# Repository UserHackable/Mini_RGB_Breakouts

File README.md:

## Mini_Arduino_3mm 

### Board dimensions

* (80000, 50000) original units
* (0.8000, 0.5000) inches
* (20.3200, 12.7000) mm

[gerbers](Mini_Arduino_3mm_gerber.zip?raw=true)

| Front | Back |
| --- | --- |
|  |  |

## Mini_Arduino_4mm_Oval 

### Board dimensions

* (80000, 50000) original units
* (0.8000, 0.5000) inches
* (20.3200, 12.7000) mm

[gerbers](Mini_Arduino_4mm_Oval_gerber.zip?raw=true)

| Front | Back |
| --- | --- |
|  |  |

## Mini_Arduino_5mm 

### Board dimensions

* (90000, 66246) original units
* (0.9000, 0.6625) inches
* (22.8600, 16.8265) mm

[gerbers](Mini_Arduino_5mm_gerber.zip?raw=true)

| Front | Back |
| --- | --- |
|  |  |

## Mini_Arduino_5mm_RGB 

### Board dimensions

* (80000, 50000) original units
* (0.8000, 0.5000) inches
* (20.3200, 12.7000) mm

[gerbers](Mini_Arduino_5mm_RGB_gerber.zip?raw=true)

| Front | Back |
| --- | --- |
|  |  |

## Mini_Oval 

### Board dimensions

* (65000, 60000) original units
* (0.6500, 0.6000) inches
* (16.5100, 15.2400) mm

[gerbers](Mini_Oval_gerber.zip?raw=true)

| Front | Back |
| --- | --- |
|  |  |

## Mini_RGB 

### Board dimensions

* (60000, 60000) original units
* (0.6000, 0.6000) inches
* (15.2400, 15.2400) mm

[gerbers](Mini_RGB_gerber.zip?raw=true)

| Front | Back |
| --- | --- |
|  |  |

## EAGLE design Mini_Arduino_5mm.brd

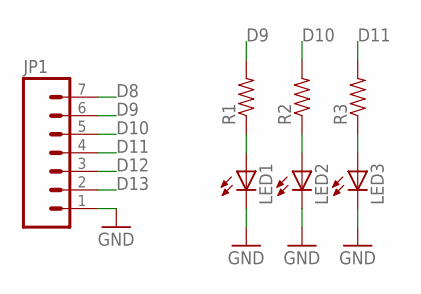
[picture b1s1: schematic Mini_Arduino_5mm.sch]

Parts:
JP1: M07; 1X07
LED1, LED2, LED3: LED5MM
R1, R2, R3: RESISTORAXIAL-0.3; AXIAL-0.3

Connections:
D8: JP1.7
D9: JP1.6, R1.P$2 (2)
D10: JP1.5, R2.P$2 (2)
D11: JP1.4, R3.P$2 (2)
D12: JP1.3
D13: JP1.2
GND: JP1.1, LED1.K (C), LED2.K (C), LED3.K (C)
unnamed: LED1.A, R1.P$1 (1)
unnamed: LED2.A, R2.P$1 (1)
unnamed: LED3.A, R3.P$1 (1)

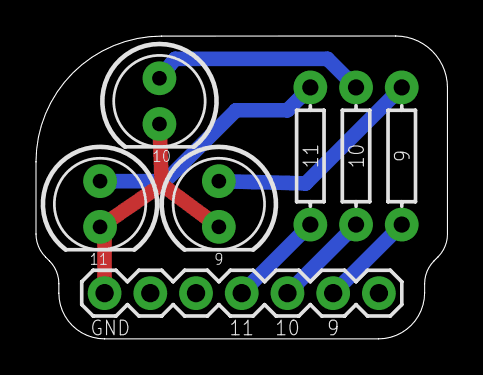
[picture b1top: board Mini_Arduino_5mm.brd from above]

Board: 2 copper layers, 22.9 x 16.8 mm, 7 parts (0 on the bottom side), 7 nets.

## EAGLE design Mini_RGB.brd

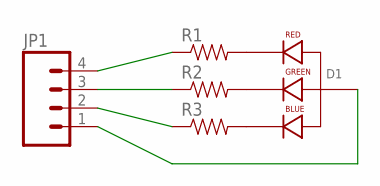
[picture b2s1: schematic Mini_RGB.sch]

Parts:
D1: LED-RGB-CA-THRUDIFFUSE; LED-RGB-THRU
JP1: M04PTH; 1X04
R1, R2, R3: RESISTORAXIAL-0.3; AXIAL-0.3

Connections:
B: JP1.2, R3.P$1 (1)
C: D1.2 (ANODE), JP1.1
G: JP1.3, R2.P$1 (1)
unnamed: D1.1 (RED_CATHODE), R1.P$2 (2)
unnamed: D1.3 (GREEN_CATHODE), R2.P$2 (2)
unnamed: D1.4 (BLUE_CATHODE), R3.P$2 (2)
R: JP1.4, R1.P$1 (1)

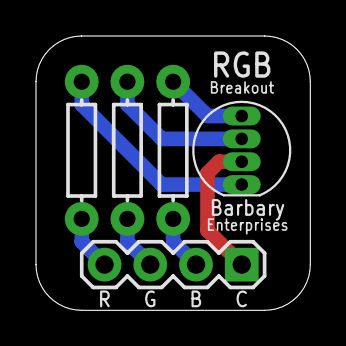
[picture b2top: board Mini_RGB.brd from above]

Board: 2 copper layers, 15.2 x 15.2 mm, 5 parts (0 on the bottom side), 7 nets.

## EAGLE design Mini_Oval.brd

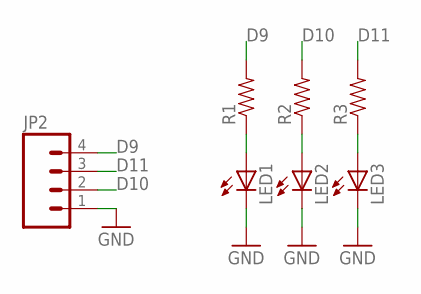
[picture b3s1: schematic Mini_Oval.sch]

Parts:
JP2: M04PTH; 1X04
LED1, LED2, LED3: LEDOVAL; LED-OVAL
R1, R2, R3: RESISTORAXIAL-0.3; AXIAL-0.3

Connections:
D9: JP2.4, R1.P$2 (2)
D10: JP2.2, R2.P$2 (2)
D11: JP2.3, R3.P$2 (2)
GND: JP2.1, LED1.CATHODE (C), LED2.CATHODE (C), LED3.CATHODE (C)
unnamed: LED1.ANODE (A), R1.P$1 (1)
unnamed: LED2.ANODE (A), R2.P$1 (1)
unnamed: LED3.ANODE (A), R3.P$1 (1)

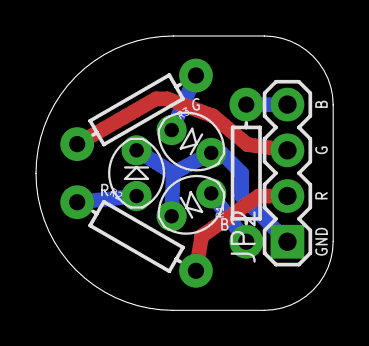
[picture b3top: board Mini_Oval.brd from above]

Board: 2 copper layers, 16.5 x 15.2 mm, 7 parts (0 on the bottom side), 7 nets.

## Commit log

2016-04-08 from Makefile

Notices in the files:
parts and their libraries:
SparkFun-Connectors: Licensing: Creative Commons ShareAlike 4.0 International - https://creativecommons.org/licenses/by-sa/4.0
